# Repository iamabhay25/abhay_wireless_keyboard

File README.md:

# Abhay's Wireless Keyboard
# VELUNE
This is my wireless keyboard for everyday personal use.<br><br>
I made this because I didn't have a keyboard and instead of going to the store and buying one, I thought, "why not build one myself?".<br><br>
So I set out on my pursuit to build a custom keyboard which, as I learned, has a lot of things to learn to get it right.<br><br>
However, in the end, I gained a lot of knowledge on the seemingly simple art of designing a keyboard and got a chance to design something that I was proud of.<br><br>
Using my keyboard is like any other keyboard, so you can just start by typing!<br><br>
Overall, I really enjoyed doing this.<br><br>
Credits for Hackclub / Blueprint for sponsoring this.
<br>
______________________________________________________
Bill of Materials:<br>
<br>
Switches:<br>
78 × GATERON Milky Yellow Cherry MX-style switches: $27.74<br>   

<br>
<br>
Electronics:<br>
1 × Custom PCB (78-key): $43.98<br>

_____________________________________

1 × Raspberry Pi Pico<br>
+<br>
78 × Diodes (1N4148)<br>
+<br>
Raspberry Pi Pico Header Pins<br>
+<br>
PCB Mount Stabilizers<br>
+<br>
Keycap Set<br><br>

= $25.78 / with free shipping

<br>
Case Assembly:<br>
8 × M3 screws (8mm length): $4.66<br>
<br>
Case Parts<br>
Top case, bottom case: (PRINTING LEGION) (SHIPPING: $5)<br>
<br>
Final Count Summary<br>
Switches: 78<br>
Diodes: 78<br>
Screws: 8 total (M3)<br>
Microcontroller: 1 Pico<br>
FINAL COST: $107.16$<br>
<br>

____________________________________

Schematic:
<br>
<br><br>
PCB:<br>
<br>
<br>
<br><br>
Wireless Keyboard Top Case CAD:<br>
<br>
<br><br>
Wireless Keyboard Bottom Case CAD:<br>
<br>
<br><br>
Final Wireless Keyboard Assembly:<br>
<br>
<br>
<br><br>

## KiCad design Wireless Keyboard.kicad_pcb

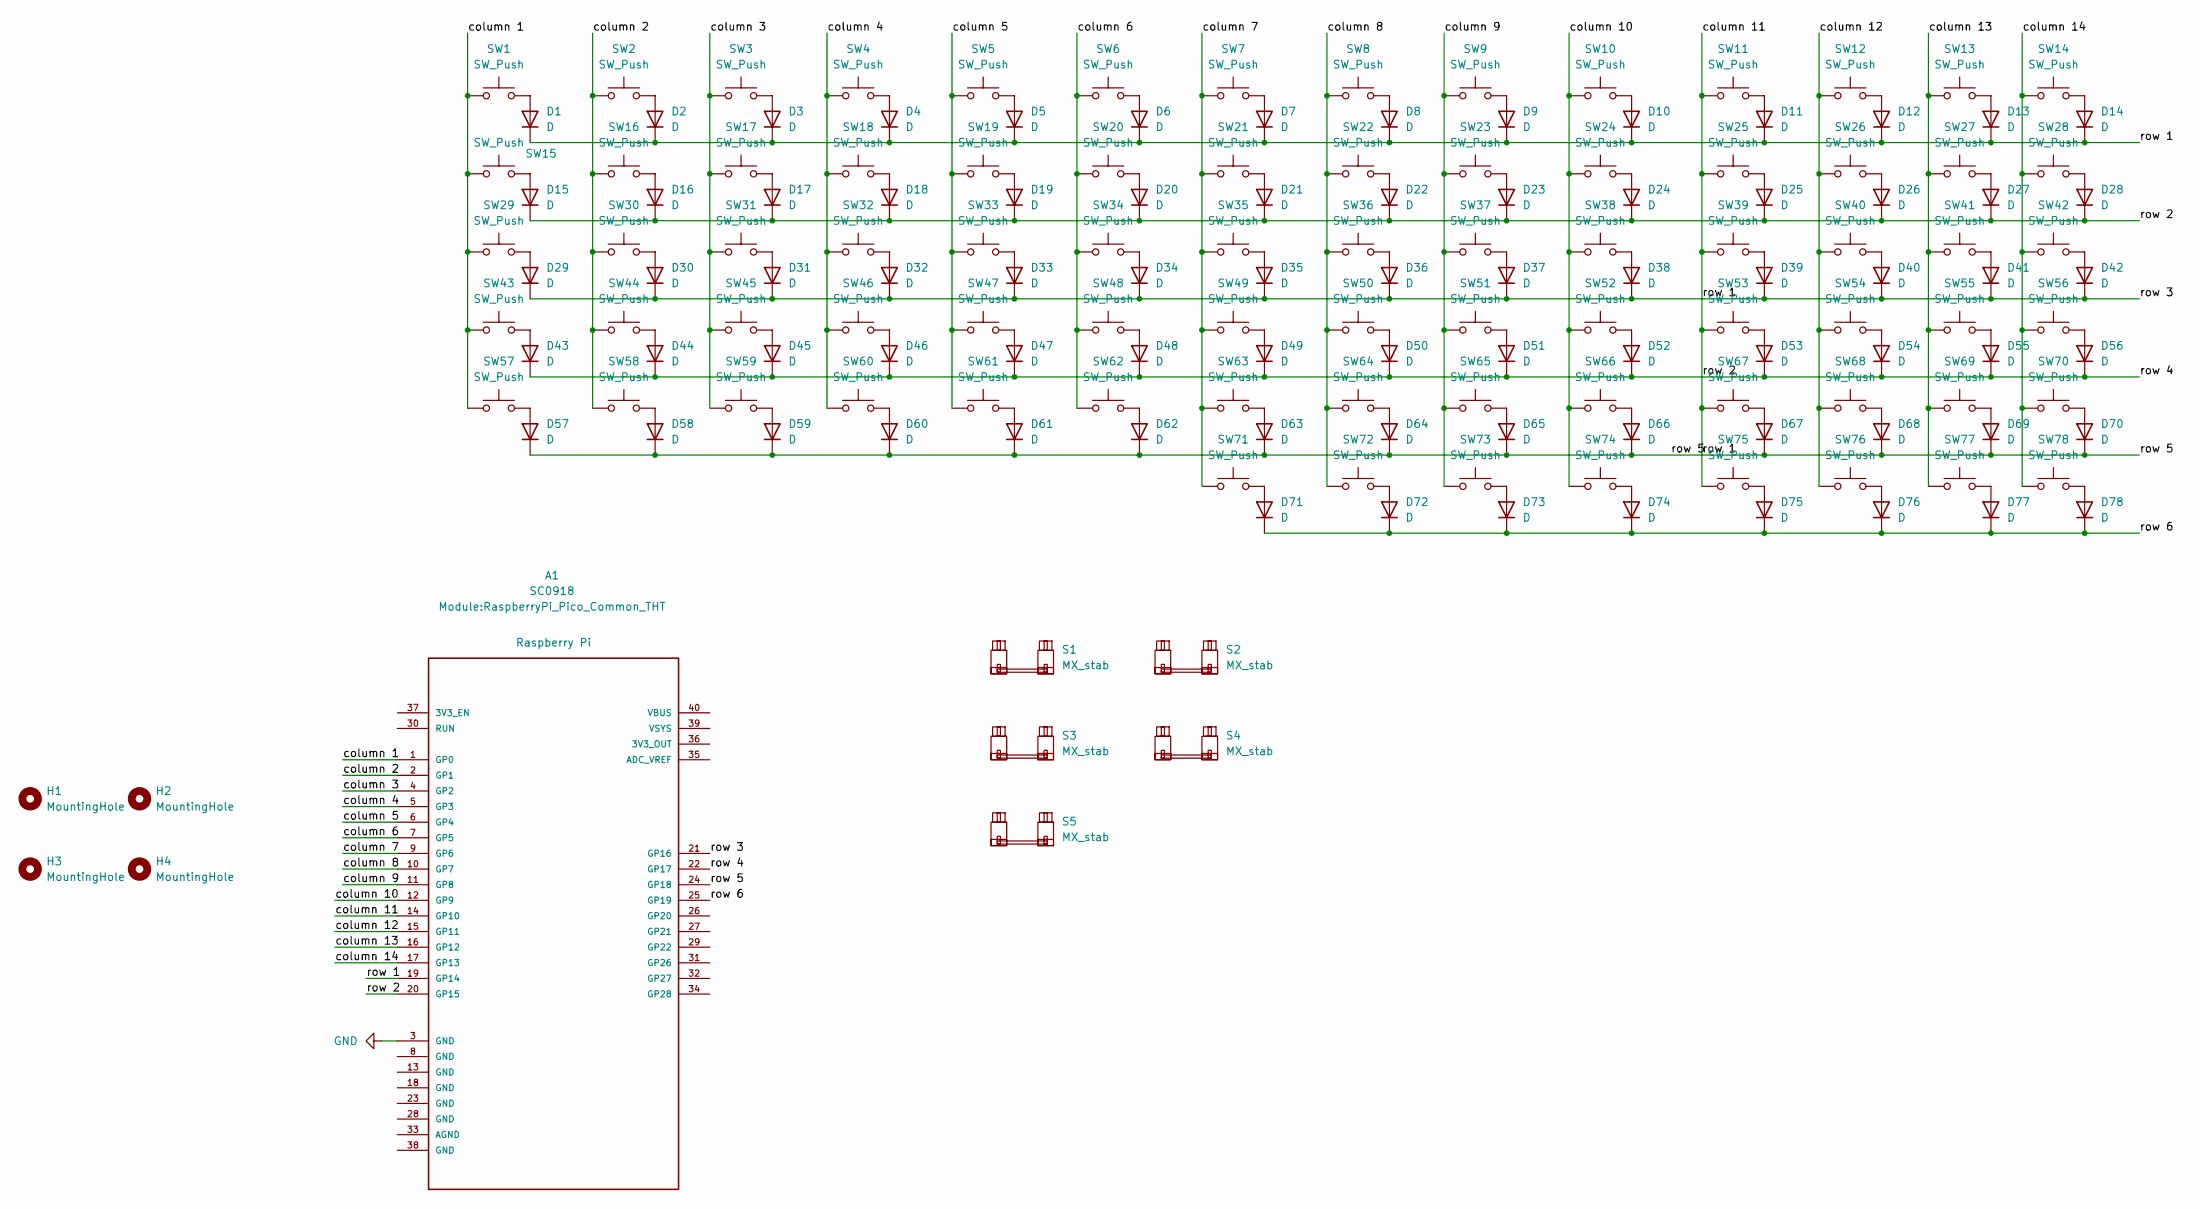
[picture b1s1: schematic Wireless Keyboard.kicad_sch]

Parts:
A1: SC0918; RaspberryPi_Pico_Common_THT; PARTREV 1.6
D1, D2, D3, D4, D5, D6, D7, D8, D9, D10, D11, D12, D13, D14, D15, D16, D17, D18, D19, D20, D21, D22, D23, D24, D25, D26, D27, D28, D29, D30, D31, D32, D33, D34, D35, D36, D37, D38, D39, D40, D41, D42, D43, D44, D45, D46, D47, D48, D49, D50, D51, D52, D53, D54, D55, D56, D57, D58, D59, D60, D61, D62, D63, D64, D65, D66, D67, D68, D69, D70, D71, D72, D73, D74, D75, D76, D77, D78: D; D_SOD-123
H1, H2, H3, H4: MountingHole; MountingHole_3.2mm_M3
S1, S2: MX_stab; SW_MX_1.75u
S3, S4: MX_stab; STAB_MX_2.25u
S5: MX_stab; STAB_MX_6.25u
SW1, SW28, SW29, SW72: SW_Push; SW_Cherry_MX_1.50u_PCB
SW2, SW3, SW4, SW5, SW6, SW7, SW8, SW9, SW10, SW11, SW12, SW13, SW14, SW15, SW16, SW17, SW18, SW19, SW20, SW21, SW22, SW23, SW24, SW25, SW26, SW27, SW30, SW31, SW32, SW33, SW34, SW35, SW36, SW37, SW38, SW39, SW40, SW41, SW42, SW44, SW45, SW46, SW47, SW48, SW49, SW50, SW51, SW52, SW53, SW54, SW57, SW58, SW59, SW60, SW61, SW62, SW63, SW64, SW65, SW66, SW75, SW76, SW77, SW78: SW_Push; SW_Cherry_MX_1.00u_PCB
SW43, SW55, SW70: SW_Push; SW_Cherry_MX_1.75u_PCB
SW56, SW67: SW_Push; SW_Cherry_MX_2.25u_PCB
SW68, SW69, SW73, SW74: SW_Push; SW_Cherry_MX_1.25u_PCB
SW71: SW_Push; SW_Cherry_MX_6.25u_PCB

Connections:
/column 1: A1.1 (GP0), SW1.1, SW15.1, SW29.1, SW43.1, SW57.1
/column 2: A1.2 (GP1), SW2.1, SW16.1, SW30.1, SW44.1, SW58.1
/column 3: A1.4 (GP2), SW3.1, SW17.1, SW31.1, SW45.1, SW59.1
/column 4: A1.5 (GP3), SW4.1, SW18.1, SW32.1, SW46.1, SW60.1
/column 5: A1.6 (GP4), SW5.1, SW19.1, SW33.1, SW47.1, SW61.1
/column 6: A1.7 (GP5), SW6.1, SW20.1, SW34.1, SW48.1, SW62.1
/column 7: A1.9 (GP6), SW7.1, SW21.1, SW35.1, SW49.1, SW63.1, SW71.1
/column 8: A1.10 (GP7), SW8.1, SW22.1, SW36.1, SW50.1, SW64.1, SW72.1
/column 9: A1.11 (GP8), SW9.1, SW23.1, SW37.1, SW51.1, SW65.1, SW73.1
/column 10: A1.12 (GP9), SW10.1, SW24.1, SW38.1, SW52.1, SW66.1, SW74.1
/column 11: A1.14 (GP10), A1.19 (GP14), A1.20 (GP15), A1.21 (GP16), A1.22 (GP17), A1.24 (GP18), D1.1 (K), D2.1 (K), D3.1 (K), D4.1 (K), D5.1 (K), D6.1 (K), D7.1 (K), D8.1 (K), D9.1 (K), D10.1 (K), D11.1 (K), D12.1 (K), D13.1 (K), D14.1 (K), D15.1 (K), D16.1 (K), D17.1 (K), D18.1 (K), D19.1 (K), D20.1 (K), D21.1 (K), D22.1 (K), D23.1 (K), D24.1 (K), D25.1 (K), D26.1 (K), D27.1 (K), D28.1 (K), D29.1 (K), D30.1 (K), D31.1 (K), D32.1 (K), D33.1 (K), D34.1 (K), D35.1 (K), D36.1 (K), D37.1 (K), D38.1 (K), D39.1 (K), D40.1 (K), D41.1 (K), D42.1 (K), D43.1 (K), D44.1 (K), D45.1 (K), D46.1 (K), D47.1 (K), D48.1 (K), D49.1 (K), D50.1 (K), D51.1 (K), D52.1 (K), D53.1 (K), D54.1 (K), D55.1 (K), D56.1 (K), D57.1 (K), D58.1 (K), D59.1 (K), D60.1 (K), D61.1 (K), D62.1 (K), D63.1 (K), D64.1 (K), D65.1 (K), D66.1 (K), D67.1 (K), D68.1 (K), D69.1 (K), D70.1 (K), SW11.1, SW25.1, SW39.1, SW53.1, SW67.1, SW75.1
/column 12: A1.15 (GP11), SW12.1, SW26.1, SW40.1, SW54.1, SW68.1, SW76.1
/column 13: A1.16 (GP12), SW13.1, SW27.1, SW41.1, SW55.1, SW69.1, SW77.1
/column 14: A1.17 (GP13), SW14.1, SW28.1, SW42.1, SW56.1, SW70.1, SW78.1
/row 6: A1.25 (GP19), D71.1 (K), D72.1 (K), D73.1 (K), D74.1 (K), D75.1 (K), D76.1 (K), D77.1 (K), D78.1 (K)
GND: A1.3 (GND)
unnamed: D1.2 (A), SW1.2
unnamed: D2.2 (A), SW2.2
unnamed: D3.2 (A), SW3.2
unnamed: D4.2 (A), SW4.2
unnamed: D5.2 (A), SW5.2
unnamed: D6.2 (A), SW6.2
unnamed: D7.2 (A), SW7.2
unnamed: D8.2 (A), SW8.2
unnamed: D9.2 (A), SW9.2
unnamed: D10.2 (A), SW10.2
unnamed: D11.2 (A), SW11.2
unnamed: D12.2 (A), SW12.2
unnamed: D13.2 (A), SW13.2
unnamed: D14.2 (A), SW14.2
unnamed: D15.2 (A), SW15.2
unnamed: D16.2 (A), SW16.2
unnamed: D17.2 (A), SW17.2
unnamed: D18.2 (A), SW18.2
unnamed: D19.2 (A), SW19.2
unnamed: D20.2 (A), SW20.2
unnamed: D21.2 (A), SW21.2
unnamed: D22.2 (A), SW22.2
unnamed: D23.2 (A), SW23.2
unnamed: D24.2 (A), SW24.2
unnamed: D25.2 (A), SW25.2
unnamed: D26.2 (A), SW26.2
unnamed: D27.2 (A), SW27.2
unnamed: D28.2 (A), SW28.2
unnamed: D29.2 (A), SW29.2
unnamed: D30.2 (A), SW30.2
unnamed: D31.2 (A), SW31.2
unnamed: D32.2 (A), SW32.2
unnamed: D33.2 (A), SW33.2
unnamed: D34.2 (A), SW34.2
unnamed: D35.2 (A), SW35.2
unnamed: D36.2 (A), SW36.2
unnamed: D37.2 (A), SW37.2
unnamed: D38.2 (A), SW38.2
unnamed: D39.2 (A), SW39.2
unnamed: D40.2 (A), SW40.2
unnamed: D41.2 (A), SW41.2
unnamed: D42.2 (A), SW42.2
unnamed: D43.2 (A), SW43.2
unnamed: D44.2 (A), SW44.2
unnamed: D45.2 (A), SW45.2
unnamed: D46.2 (A), SW46.2
unnamed: D47.2 (A), SW47.2
unnamed: D48.2 (A), SW48.2
unnamed: D49.2 (A), SW49.2
unnamed: D50.2 (A), SW50.2
unnamed: D51.2 (A), SW51.2
unnamed: D52.2 (A), SW52.2
unnamed: D53.2 (A), SW53.2
unnamed: D54.2 (A), SW54.2
unnamed: D55.2 (A), SW55.2
unnamed: D56.2 (A), SW56.2
unnamed: D57.2 (A), SW57.2
unnamed: D58.2 (A), SW58.2
unnamed: D59.2 (A), SW59.2
unnamed: D60.2 (A), SW60.2
unnamed: D61.2 (A), SW61.2
unnamed: D62.2 (A), SW62.2
unnamed: D63.2 (A), SW63.2
unnamed: D64.2 (A), SW64.2
unnamed: D65.2 (A), SW65.2
unnamed: D66.2 (A), SW66.2
unnamed: D67.2 (A), SW67.2
unnamed: D68.2 (A), SW68.2
unnamed: D69.2 (A), SW69.2
unnamed: D70.2 (A), SW70.2
unnamed: D71.2 (A), SW71.2
unnamed: D72.2 (A), SW72.2
unnamed: D73.2 (A), SW73.2
unnamed: D74.2 (A), SW74.2
unnamed: D75.2 (A), SW75.2
unnamed: D76.2 (A), SW76.2
unnamed: D77.2 (A), SW77.2
unnamed: D78.2 (A), SW78.2

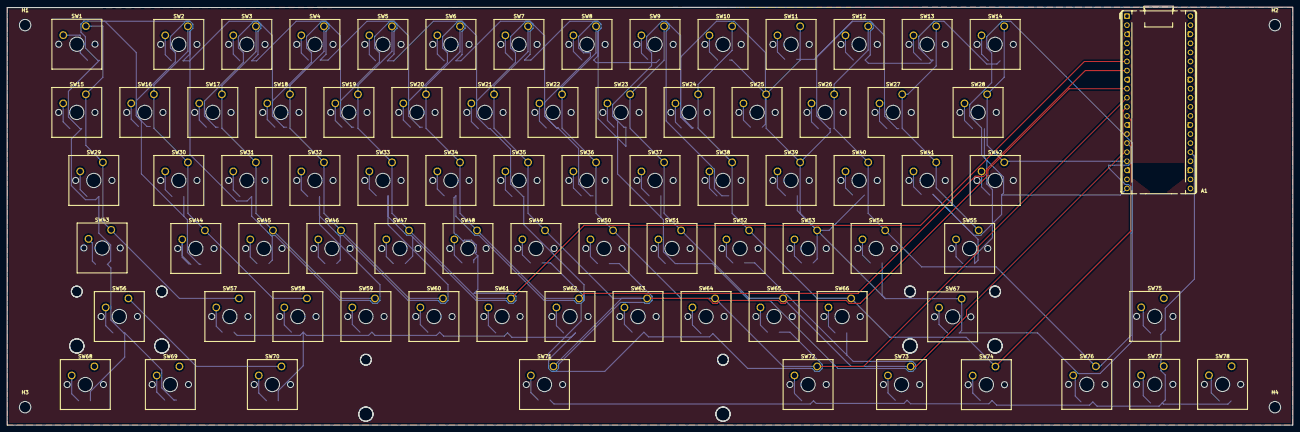
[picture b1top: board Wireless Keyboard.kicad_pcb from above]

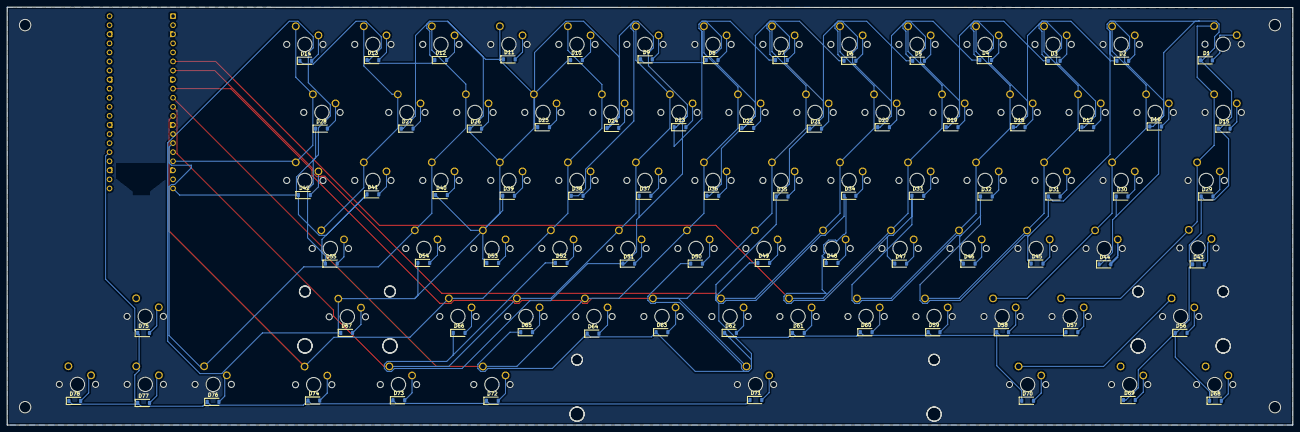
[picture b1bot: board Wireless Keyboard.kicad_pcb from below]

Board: 4 copper layers, 360.0 x 117.0 mm, 164 parts (78 on the bottom side), 93 nets.

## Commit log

2026-03-23 Expand README with Bill of Materials for keyboard
    Added a detailed Bill of Materials for the wireless keyboard project, including components and quantities.
2026-03-23 Update README with schematic and CAD images
    Added images for schematic, PCB, and CAD designs.
2026-03-23 Replace PCB image in README
    Updated PCB image in README with a new screenshot.
2026-03-23 Update project title in README
2026-03-23 Rename Wireless Keyboard.kicad_pcb to asdwasds
2026-03-23 Rename asdwasds to wireless keyboard.kicad/pcb
2026-03-23 Rename pcb to PCB
2026-03-23 Rename Wireless Keyboard.kicad_pcb to PCB/Wireless Keyboard.kicad_pcb
2026-03-23 Rename Wireless Keyboard.kicad_pro to PCB/Wireless Keyboard.kicad_pro
2026-03-23 Rename Wireless Keyboard.kicad_sch to PCB/Wireless Keyboard.kicad_sch
2026-03-23 Add wireless keyboard bottom CAD file
2026-03-23 Add wireless keyboard top CAD file
2026-03-23 Update images in README for keyboard CAD
2026-03-27 Update README with new CAD images and final build
    Added new images and updated existing ones for the wireless keyboard CAD and final build.
2026-03-27 Fix formatting for switches and keycaps section
2026-03-27 Update switch description in README
2026-03-27 Add final cost to README
2026-03-27 Update final wireless keyboard build image
2026-03-27 Rename wireless_keyboard.py to FIRMWARE/wireless_keyboard.py
2026-03-27 Update comment for matrix configuration section
2026-03-30 Revise final cost and include shipping details
    Updated final cost and added shipping cost.
2026-03-31 Rename wireless+keyboard+bottom.stp to CAD/wireless+keyboard+bottom.stp
2026-03-31 Fix HTML encoding in README.md images section
2026-03-31 Fix header formatting for VELUNE
2026-03-31 Update cost of keyboard components in README
2026-03-31 Update switch details in README
2026-04-01 Update screenshots for wireless keyboard CAD and build
2026-04-03 Revise bill of materials and update final cost
    Updated bill of materials and final cost.
2026-04-03 Fix typo in case parts description
2026-04-03 Fix formatting of final cost in README
2026-04-05 Rename wireless keyboard bottom.step to CAD/wireless keyboard bottom.step
2026-04-05 Rename wireless keyboard top.step to CAD/wireless keyboard top.step
2026-04-05 Rename wireless keyboard assembly.f3z to ASSEMBLY/wireless keyboard assembly.f3z
